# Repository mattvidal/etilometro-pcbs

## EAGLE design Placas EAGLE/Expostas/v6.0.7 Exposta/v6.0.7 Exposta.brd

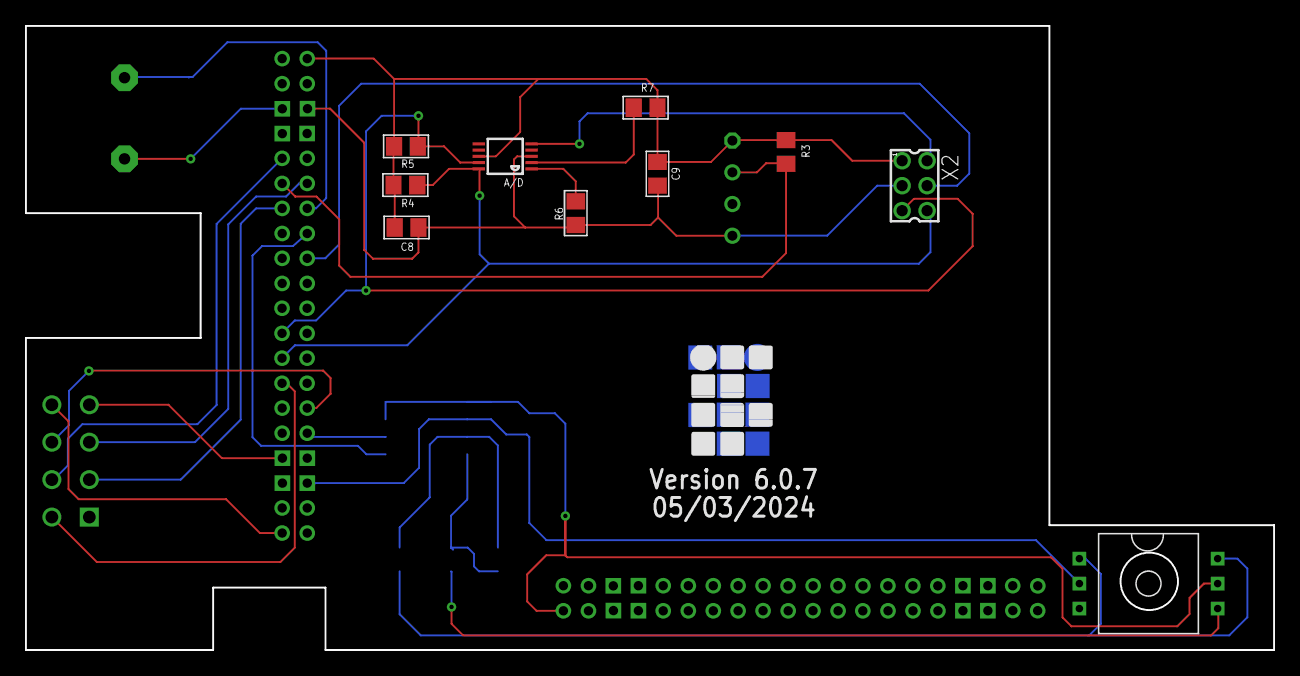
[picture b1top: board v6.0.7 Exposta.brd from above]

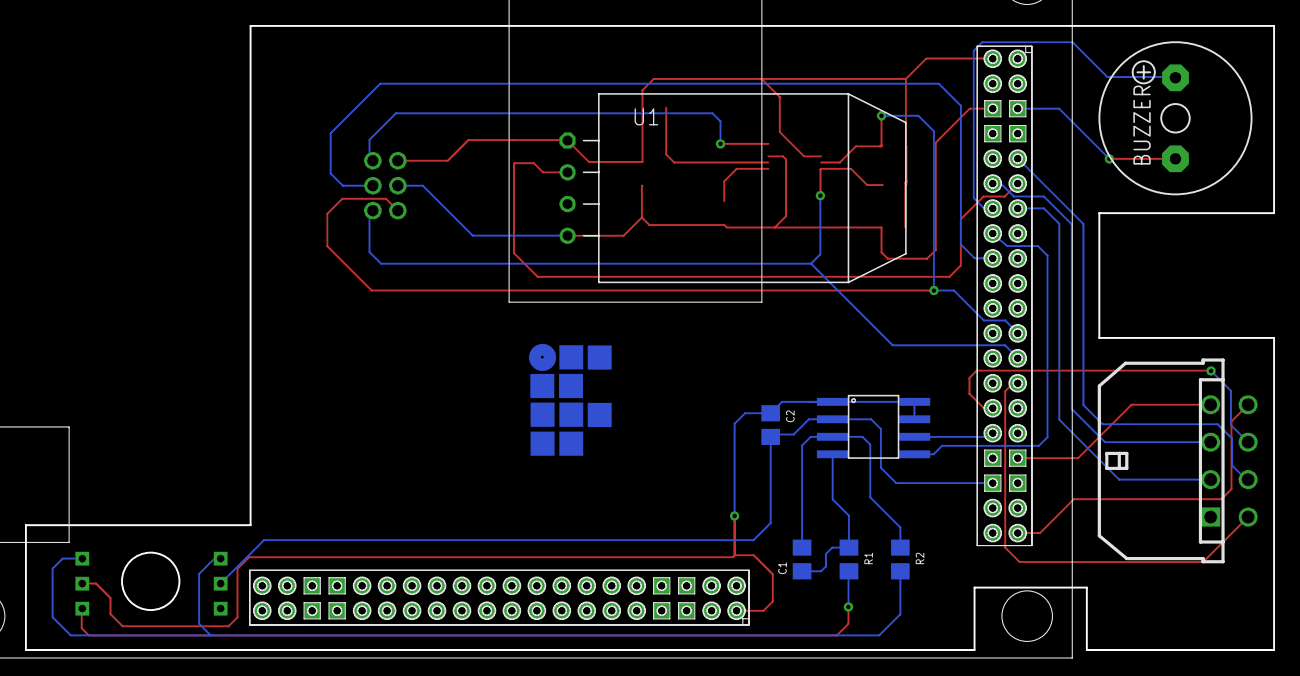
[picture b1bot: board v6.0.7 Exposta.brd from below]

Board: 2 copper layers, 100.0 x 50.0 mm, 19 parts (9 on the bottom side), 26 nets.

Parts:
A/D: ADS1115IDGST; MSOP10
BUZZER: F/QMX
C1, C2: 100n; C0805
C8, C9: 1µF; 0805
MICROFIT: 43045-0800
R1, R2: 100; R0805
R3: 10k; R0805
R4, R5, R6, R7: 10K; 0805
U1: RHT03_DHT-22/RA
U$1: WT32_SC01; WT32
U$2: HX710B; HX710B_SMD
U$3: PRESSUREPRESSURE_PTH; PRESSURE_PTH
X2: 332-06

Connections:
5V_6: MICROFIT.P$8, U$1.5V_6
ADDR: A/D.1, R6.1
ALERT: A/D.2, R7.2
A_OUT: A/D.5, X2.2
BZ: BUZZER.+, U$1.IO25_2
GND: C2.2, U$1.GND_7, U$2.AGND, U$3.2
GND14: BUZZER.-, U$1.GND_14
GND_10: MICROFIT.P$4, U$1.GND_10
GND_S: A/D.3, C8.1, C9.2, R6.2, U1.GND, U$1.GND_12, X2.3
HEAT: U$1.IO0_2, X2.4
IO2: MICROFIT.P$7, U$1.IO2_2
IO26: MICROFIT.P$3, U$1.IO26_2
IO27: MICROFIT.P$2, U$1.IO27_2
IO32: R3.2, U1.DATA, U$1.IO32_2
IO33: MICROFIT.P$6, U$1.IO33_2
IO34: MICROFIT.P$5, U$1.IO34_2
unnamed: C1.2, R2.1, U$2.INN
unnamed: C1.1, R1.1, U$2.INP
unnamed: R1.2, U$3.4
unnamed: R2.2, U$3.1, U$3.6
OUT: U$1.IO4_2, U$2.DOUT
SCK: U$1.IO5_2, U$2.SCK
SCL: A/D.10, R4.2, U$1.SCL_2, X2.6
SDA: A/D.9, R5.2, U$1.SDA_2, X2.5
VCC: C2.1, U$1.5V_4, U$2.AVDD, U$2.DVDD, U$2.VREF, U$3.5
VCC_S: A/D.8, C8.2, C9.1, R3.1, R4.1, R5.1, R7.1, U1.VDD, U$1.5V_7, X2.1

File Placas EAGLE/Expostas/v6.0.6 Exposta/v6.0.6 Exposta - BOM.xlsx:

Part | Value | MPN
A/D | ADS1115IDGST | ADS1115IDGST
BUZZER | F/QMX | CMI-1295-0585T
C1 | 100n | C0805C104K8RACAUTO
C2 | 100n | C0805C104K8RACAUTO
C8 | 1µF | GRM21BR71A105KA01K
C9 | 1µF | GRM21BR71A105KA01K
MICROFIT |  | MOLEX 43045-0800
R1 | 100 | RA73F2A100RBTDF
R2 | 100 | RA73F2A100RBTDF
R3 | 10k | RP0805FRE0710KL
R4 | 10K | RP0805FRE0710KL
R5 | 10K | RP0805FRE0710KL
R6 | 10K | RP0805FRE0710KL
R7 | 10K | RP0805FRE0710KL
U$1 |  | WT32-SC01 v3.3
U$2 |  | HX710B
U$3 |  | MPS20N0040D-GDR
U1 |  | DHT22
X2 |  | 6 Pin - 2mm Dual Row

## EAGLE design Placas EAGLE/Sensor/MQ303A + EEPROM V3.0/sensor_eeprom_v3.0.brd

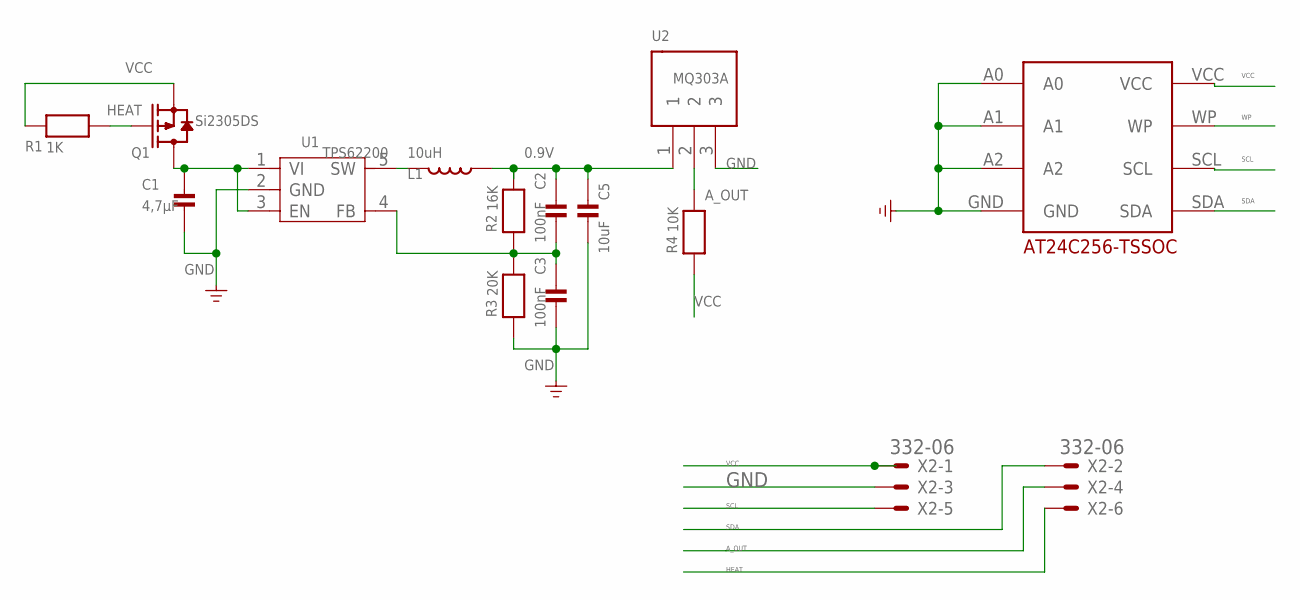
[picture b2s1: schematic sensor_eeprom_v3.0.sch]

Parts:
C1: 4,7µF; 0805
C2, C3: 100nF; 0805
C5: 10uF; 0805
L1: 10uH; PIO73
Q1: Si2305DS; SOT23
R1: 1K; 0805
R2: 16K; 0805
R3: 20K; 0805
R4: 10K; 0805
U1: TPS62200; SOT23-5
U2: MQ303A
U$1: DECADE-AT24C256-10TI-2.7; DECADE-AT24CXX
X2: 332-06

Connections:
0.9V: C2.1, C5.1, L1.2, R2.2, U2.1
A_OUT: R4.2, U2.2, X2.4
GND: C1.2, C3.2, C5.2, R3.1, U1.2 (GND), U2.3, U$1.A0, U$1.A1, U$1.A2, U$1.GND, X2.3
HEAT: Q1.1 (G), R1.2, X2.6
unnamed: C1.1, Q1.3 (D), U1.1 (VI), U1.3 (EN)
unnamed: L1.1, U1.5 (SW)
unnamed: C2.2, C3.1, R2.1, R3.2, U1.4 (FB)
SCL: U$1.SCL, X2.5
SDA: U$1.SDA, X2.2
VCC: Q1.2 (S), R1.1, R4.1, U$1.VCC, X2.1
WP: U$1.WP

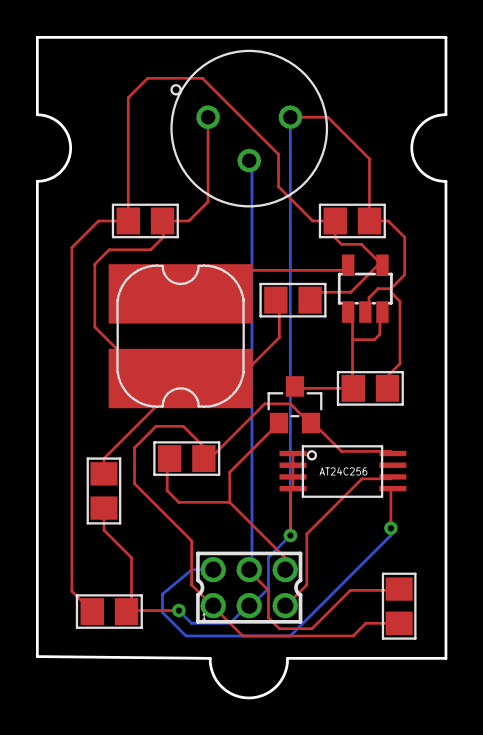
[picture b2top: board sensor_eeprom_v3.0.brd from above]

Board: 2 copper layers, 22.7 x 36.7 mm, 14 parts (0 on the bottom side), 10 nets.

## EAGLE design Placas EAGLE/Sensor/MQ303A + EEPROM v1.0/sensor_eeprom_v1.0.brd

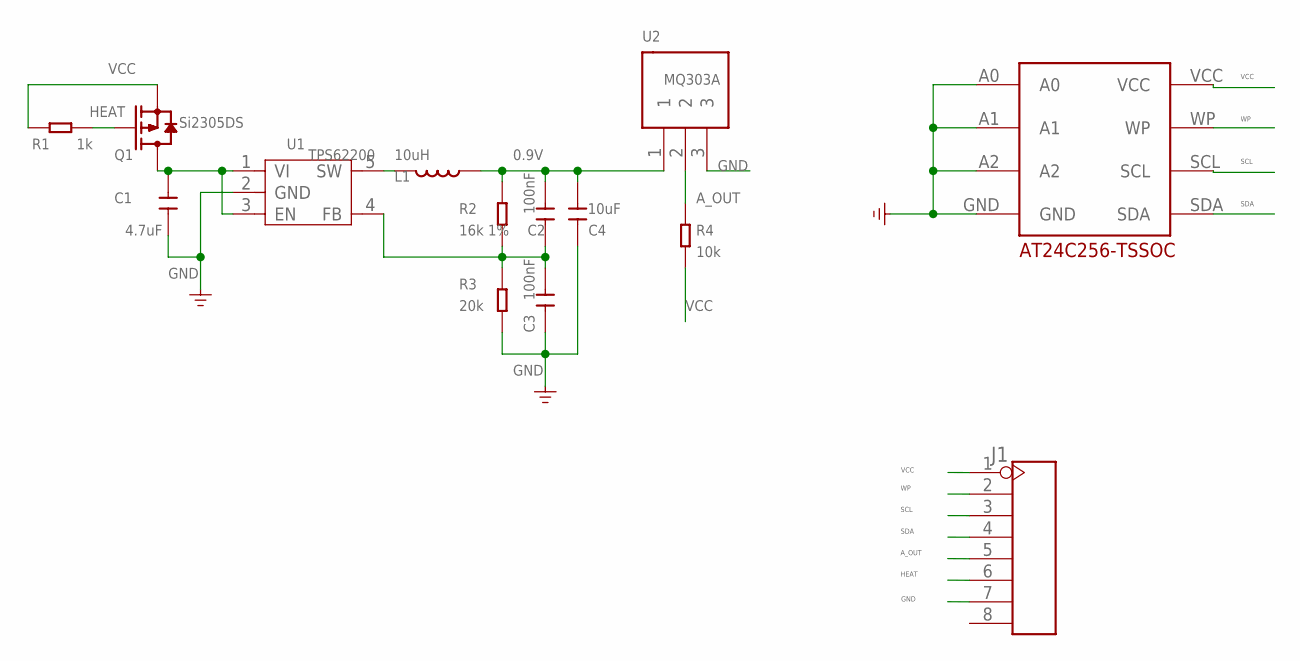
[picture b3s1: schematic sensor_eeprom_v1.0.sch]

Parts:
C1: 4.7uF; C0805
C2, C3: 100nF; C0603
C4: 10uF; C0805
J1: HEADER-8P-2.54; 8P-2.54
L1: 10uH; PIO73
Q1: Si2305DS; SOT23
R1: 1k; R0603
R2: 16k 1%; R0603
R3: 20k; R0603
R4: 10k; R0603
U1: TPS62200; SOT23-5
U2: MQ303A
U$1: DECADE-AT24C256-10TI-2.7; DECADE-AT24CXX

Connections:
0.9V: C2.2, C4.2, L1.2, R2.1, U2.1
A_OUT: J1.5, R4.1, U2.2
GND: C1.2, C3.1, C4.1, J1.7, R3.2, U1.2 (GND), U2.3, U$1.A0, U$1.A1, U$1.A2, U$1.GND
HEAT: J1.6, Q1.1 (G), R1.1
unnamed: C1.1, Q1.3 (D), U1.1 (VI), U1.3 (EN)
unnamed: L1.1, U1.5 (SW)
unnamed: C2.1, C3.2, R2.2, R3.1, U1.4 (FB)
SCL: J1.3, U$1.SCL
SDA: J1.4, U$1.SDA
VCC: J1.1, Q1.2 (S), R1.2, R4.2, U$1.VCC
WP: J1.2, U$1.WP

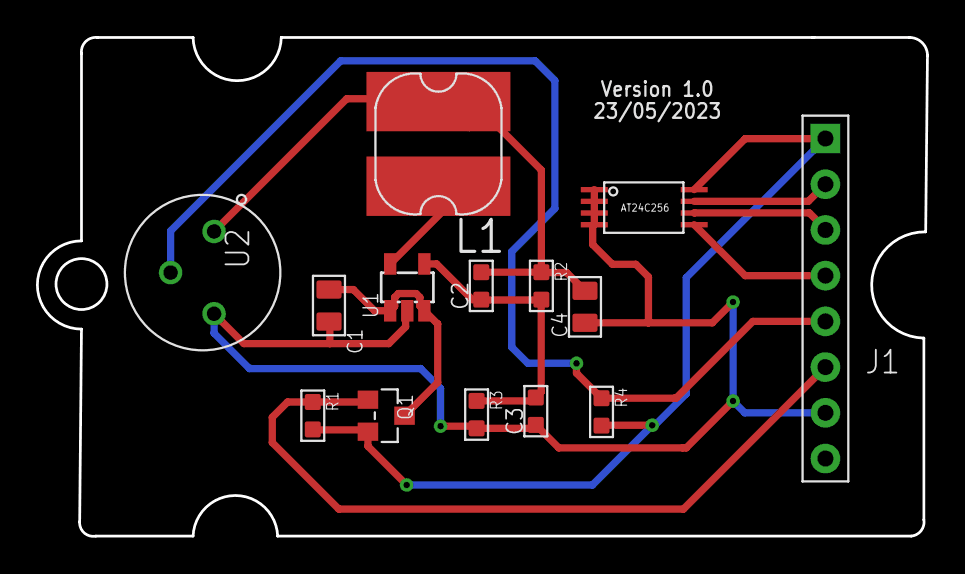
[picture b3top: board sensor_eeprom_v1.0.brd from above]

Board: 2 copper layers, 49.4 x 27.7 mm, 14 parts (0 on the bottom side), 11 nets.

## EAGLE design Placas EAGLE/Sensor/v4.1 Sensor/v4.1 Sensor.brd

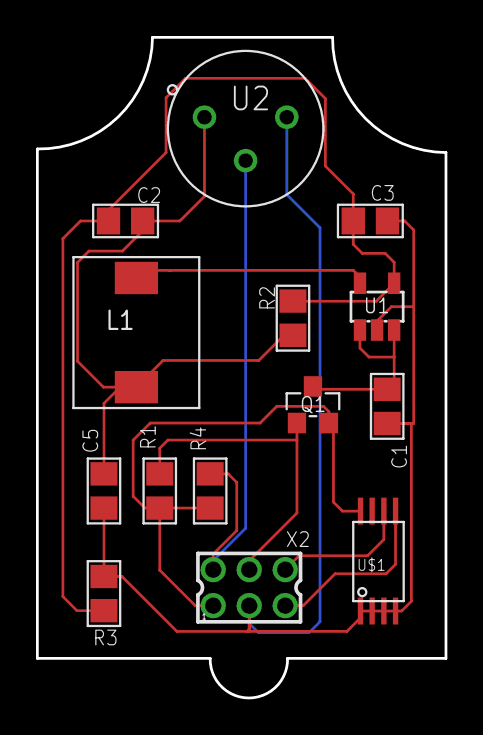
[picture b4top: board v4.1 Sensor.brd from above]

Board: 2 copper layers, 22.7 x 36.7 mm, 14 parts (0 on the bottom side), 10 nets.

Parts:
C1: 10µF; 0805
C2, C3: 100nF; 0805
C5: 4,7uF; 0805
L1: 10uH; SDR7045-100M
Q1: Si2305DS; SOT23
R1: 1K; 0805
R2: 16K; 0805
R3: 20K; 0805
R4: 10K; 0805
U1: TPS62200; SOT23-5
U2: MQ303A
U$1: DECADE-AT24C256-10TI-2.7; DECADE-AT24CXX
X2: 332-06

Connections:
0.9V: C2.1, C5.1, L1.1, R2.2, U2.1
A_OUT: R4.2, U2.2, X2.2
GND: C1.2, C3.2, C5.2, R3.1, U1.2, U2.3, U$1.A0, U$1.A1, U$1.A2, U$1.GND, X2.3
HEAT: Q1.1, R1.2, X2.4
unnamed: C1.1, Q1.3, U1.1, U1.3
unnamed: L1.2, U1.5
unnamed: C2.2, C3.1, R2.1, R3.2, U1.4
SCL: U$1.SCL, X2.6
SDA: U$1.SDA, X2.5
VCC: Q1.2, R1.1, R4.1, U$1.VCC, X2.1

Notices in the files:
parts and their libraries:
DECADE-libraries20151104: Licensing: Creative Commons ShareAlike 4.0 International - https://creativecommons.org/licenses/by-sa/4.0
